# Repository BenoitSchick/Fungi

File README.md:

# Projet Fungi

The goal of this project is to measure the impedance of bags containing mycelium in order to observe how mycelium growth influences impedance. With this information, we aim to determine whether the mycelium is fully developed in the bags or if there are areas with little or no growth.

## Operation

The idea is to measure the impedance of the mycelium over several weeks to observe its evolution. Each measurement consists of a frequency sweep from 1 kHz to 100 kHz, taken every 5 minutes.  

The measurements from the Evaluation Board (EVAL-AD5940BIOZ) are retrieved via UART by a Raspberry Pi. The Raspberry Pi then synchronizes this data with Google Drive, making the measurements accessible from anywhere.

The measurement process is triggered by the Raspberry Pi. The reason for this is that up to four boards can be placed on the same bag, and the Raspberry Pi coordinates the measurements from each board to prevent interference.

## Material used
- Precision Impedance Analyzer - Agilent 4294A
- ECG Electrodes
- 4 x Bio-Electric Evaluation Board - EVAL-AD5940BIOZ
- Raspberry pi model 3B+

## Installation / Configuration
### Flashing the Evaluation Board

The first step is to install the Keil IDE to compile and program the Evaluation Board by following this setup guide: https://wiki.analog.com/resources/eval/user-guides/eval-ad5940/tools/keil_setup_guide  

The code used to program the evaluation board is located in the following folder: _Fungi/EVAL-AD590ELCZ_Pain/ad5940-examples-master/ad5940-examples-master/examples/AD5940_BIA_

This code is based on the official repository: https://github.com/analogdevicesinc/ad5940-examples  

With this code, the evaluation board performs a frequency sweep to measure impedance only when it receives a trigger signal on **pin GP4** from the Raspberry Pi.

### Raspberry Pi Configuration

The Raspberry Pi runs two Python scripts in the background, located in:  
_Fungi/EVAL-AD590ELCZ_Pain/python_Code_

- com_ports.py 
- Measurement_synchronization.py  

The first script retrieves data from each COM port to which the four AD5940 boards are connected. It stores the data in CSV files, one per COM port, in the folder: _Fungi/EVAL-AD590ELCZ_Pain/python_Code/Measurement_

The second script sends trigger pulses to the **GP4 pins** of the four evaluation boards to start measurements. It also coordinates measurements between the boards to avoid interference. Additionally, it synchronizes the data in the `Measurement` folder with a `measure_impedance` folder on Google Drive using `rclone`.

#### Python Installation

- Install Python 3 and pip:

```bash
sudo apt update && sudo apt upgrade -y
sudo apt install python3 python3-pip -y
```
- Create and activate a virtual environment:

```bash
python3 -m venv mon_env
source mon_env/bin/activate
```

- Install required libraries:
```bash
# Library for serial communication
pip install pyserial
# Library to control Raspberry Pi GPIO
pip install RPi.GPIO
```

#### Google Drive Remote Configuration
To synchronize the local `Measurement` folder with a remote folder on Google Drive, install and configure `rclone`:

```bash
# Install rclone
sudo apt install rclone
# Configure rclone
rclone config
```

#### Create Services to Run Python Scripts
The two python scripts (_com_ports.py_ and _Measurement_synchronization.py_) are run as background services on Linux. This ensures they start automatically when the Raspberry Pi powers on. The service files are located in: _/etc/systemd/system_

- *read_ports.service* : Runs _com_ports.py_

```bash
[Unit]
Description=Measurement System (Serial)
After=network.target

[Service]
ExecStart=/home/fr1boise/Documents/Fungi/EVAL-AD590ELCZ_Pain/python_Code/.venv/bin/python3 /home/fr1boise/Documents/Fungi/EVAL-AD590ELCZ_Pain/python_Code/com_ports.py
WorkingDirectory=/home/fr1boise/Documents/Fungi/EVAL-AD590ELCZ_Pain/python_Code
Restart=always
RestartSec=5
User=fr1boise

PrivilegesStartOnly=true

[Install]
WantedBy=multi-user.target
```
- *measure_syncro.service* : Runs _Measurement_synchronization.py_

```bash
[Unit]
Description=Measurement System (Synchronisation)
After=network.target

[Service]
ExecStart=/home/fr1boise/Documents/Fungi/EVAL-AD590ELCZ_Pain/python_Code/.venv/bin/python3 /home/fr1boise/Documents/Fungi/EVAL-AD590ELCZ_Pain/python_Code/Measurement_synchronization.py
WorkingDirectory=/home/fr1boise/Documents/Fungi/EVAL-AD590ELCZ_Pain/python_Code
Restart=always
RestartSec=5
User=fr1boise

PrivilegesStartOnly=true

[Install]
WantedBy=multi-user.target
```

- Commands to enable and start a service:

```bash
sudo systemctl enable name.service
sudo systemctl start name.service
```

# EVAL-AD777xFMCZ - Electrophysiological measurement
- *ad777.service* : Runs the ad777 executable

```bash
[Unit]
Description=Electrophysiological measurement (AD777)
After=network.target

[Service]
ExecStart=/home/fr1boise/Documents/Fungi/ADC/AD777_code/ad777
WorkingDirectory=/home/fr1boise/Documents/Fungi/ADC/AD777_code/
Restart=always
RestartSec=5
User=root

[Install]
WantedBy=multi-user.target
```

- *sync_ADC.sh* : Script to synchronize data on Google Drive
```bash
#!/bin/bash

mkdir -p /home/fr1boise/Documents/Fungi/adc_snapshot

rsync -a --delete --inplace \
/home/fr1boise/Documents/Fungi/ADC/AD777_code/Measurement_ADC/ \
/home/fr1boise/Documents/Fungi/adc_snapshot

rclone copy /home/fr1boise/Documents/Fungi/adc_snapshot gdrive:mesure_ADC \
  --transfers=4 \
  --fast-list \
  --drive-use-trash=false
```

# Tailscale
## Installation 

- Enable ssh server
```bash
sudo raspi-config
```

- Installation:
```bash
curl -fsSL https://tailscale.com/install.sh | sh
```
- start the Tailscale client
```bash
sudo tailscale up --ssh
```
if it don't work : 
```bash
sudo tailscale up --force-reauth
```

- connect to raspberry
```bash
ssh fr1boise@100.98.6.121
```

- Transfer file from Raspberry Pi to Laptop (Laptop and Raspberry must be added to tailscale)
```bash
scp /home/fr1boise/Documents/Fungi/adc_snapshot/channel0 beuns/@100.91.175.60:/home/beuns/Documents
```

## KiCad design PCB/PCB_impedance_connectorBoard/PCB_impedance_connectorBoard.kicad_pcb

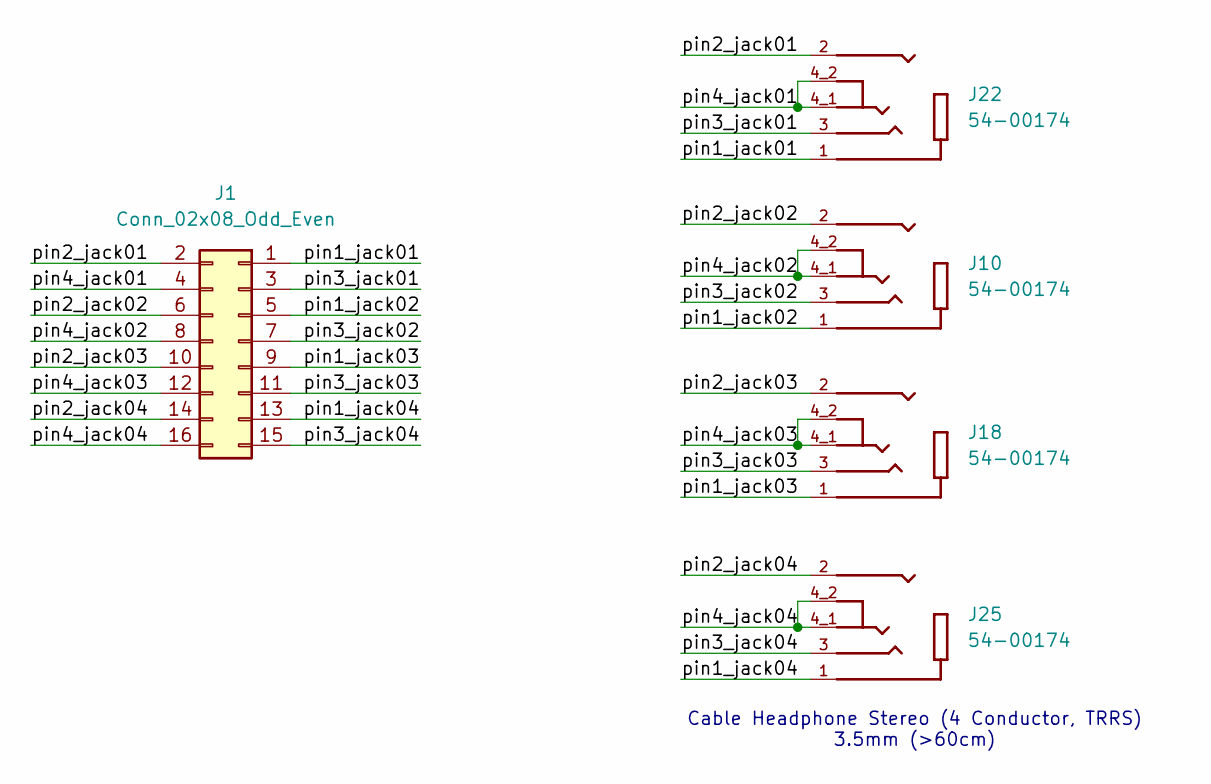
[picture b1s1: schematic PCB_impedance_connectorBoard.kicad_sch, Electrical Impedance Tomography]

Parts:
J1: Conn_02x08_Odd_Even; PinHeader_2x08_P2.54mm_Vertical; Manufacturer Part Number SSK03-MPH-254-B8; Digikey Pat Number 2223-SSK03-MPH-254-B8-ND
J10, J18, J22, J25: 54-00174; connJack_4cond_54-00174; Manufacturer Part Number 54-00174; Digikey Part Number 839-54-00174CT-ND

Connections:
/pin1_jack01: J1.1, J22.1
/pin1_jack02: J1.5, J10.1
/pin1_jack03: J1.9, J18.1
/pin1_jack04: J1.13, J25.1
/pin2_jack01: J1.2, J22.2
/pin2_jack02: J1.6, J10.2
/pin2_jack03: J1.10, J18.2
/pin2_jack04: J1.14, J25.2
/pin3_jack01: J1.3, J22.3
/pin3_jack02: J1.7, J10.3
/pin3_jack03: J1.11, J18.3
/pin3_jack04: J1.15, J25.3
/pin4_jack01: J1.4, J22.4_1, J22.4_2
/pin4_jack02: J1.8, J10.4_1, J10.4_2
/pin4_jack03: J1.12, J18.4_1, J18.4_2
/pin4_jack04: J1.16, J25.4_1, J25.4_2

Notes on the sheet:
Cable Headphone Stereo (4 Conductor, TRRS) 3.5mm (>60cm)

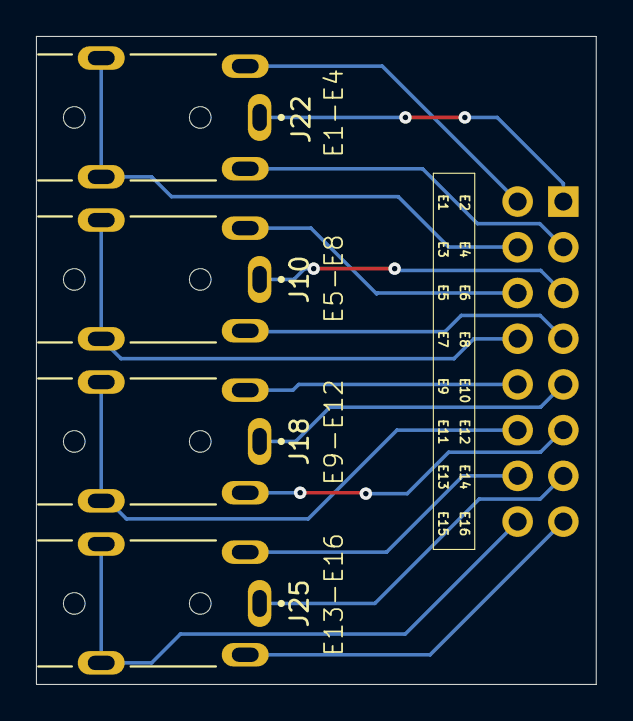
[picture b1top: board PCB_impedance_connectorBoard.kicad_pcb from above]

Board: 2 copper layers, 31.1 x 36.0 mm, 5 parts (1 on the bottom side), 16 nets.

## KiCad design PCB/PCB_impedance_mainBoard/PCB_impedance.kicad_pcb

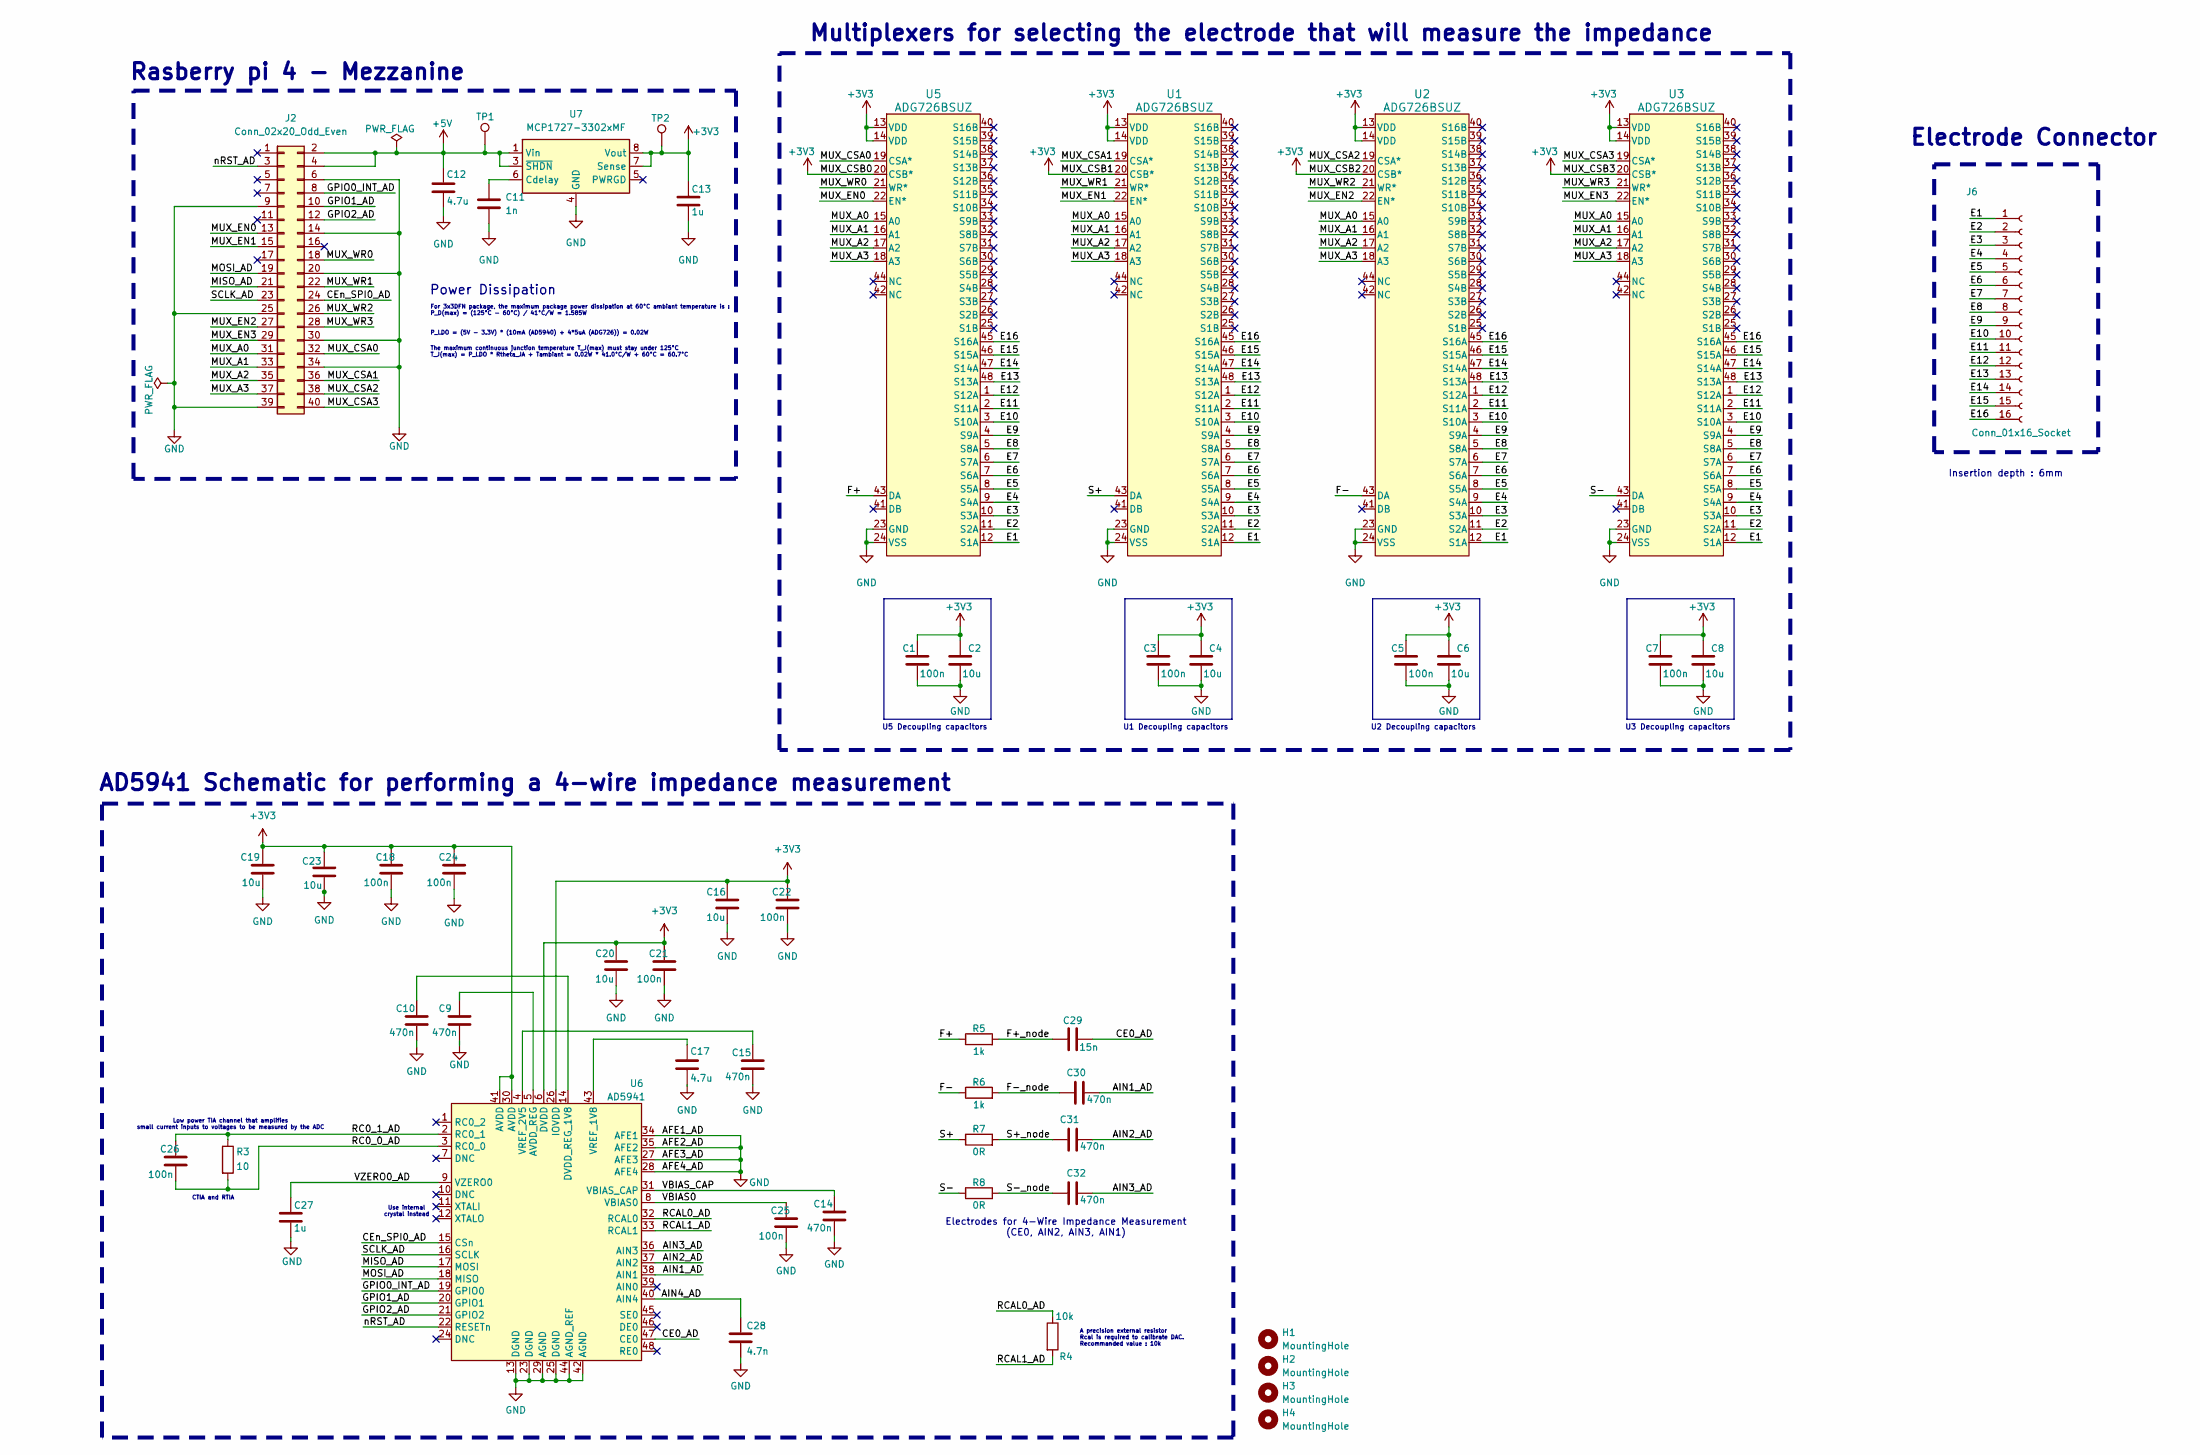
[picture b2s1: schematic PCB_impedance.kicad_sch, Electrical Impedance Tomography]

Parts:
C1, C3, C5, C7: 100n; C_0603_1608Metric; Manufacturer Part Number C0805F104K1RACAUTO; Digikey Part Number 399-C0805F104K1RACAUTODKR-ND
C2, C4, C6, C8: 10u; C_0603_1608Metric; Manufacturer Part Number GRM21BR71A106KA73K; Digikey Part Number 490-14381-6-ND
C9, C10, C14, C15, C30, C31, C32: 470n; C_0603_1608Metric; Manufacturer Part Number GCM188R71C474KA55D; Digikey Part Number 490-4775-6-ND
C11: 1n; C_0603_1608Metric; Manufacturer Part Number C0603C102K5RACTU; Digikey Part Number 399-C0603C102K5RACTUDKR-ND
C12, C17: 4.7u; C_0805_2012Metric; Manufacturer Part Number GRM21BR61H475KE51L; Digikey Part Number 490-10751-6-ND
C13, C27: 1u; C_0805_2012Metric; Manufacturer Part Number C0805C105K3RACTU; Digikey Part Number 399-C0805C105K3RACTUDKR-ND
C16, C19, C20, C23: 10u; C_0805_2012Metric; Manufacturer Part Number GRM21BR71A106KA73K; Digikey Part Number 490-14381-6-ND
C18, C21, C22, C24, C25, C26: 100n; C_0805_2012Metric; Manufacturer Part Number C0805F104K1RACAUTO; Digikey Part Number 399-C0805F104K1RACAUTODKR-ND
C28: 4.7n; C_0603_1608Metric; Manufacturer Part Number GRM1885C1H472JA01D; Digikey Part Number 490-9669-6-ND
C29: 15n; C_0603_1608Metric; Manufacturer Part Number C0603C153K5RACTU; Digikey Part Number 399-C0603C153K5RACTUDKR-ND
H1, H2, H3, H4: MountingHole; MountingHole_2.7mm_Pad
J2: Conn_02x20_Odd_Even; PinSocket_2x20_P2.54mm_Vertical
J6: Conn_01x16_Socket; conn_1x16_PPPC082LFBN-RC; Manufacturer Part Number PPPC082LFBN-RC; Digikey Part Number S7111-ND
R3: 10; R_0805_2012Metric; Manufacturer Part Number RT0805BRD0710RL; Digikey Part Number YAG4820DKR-ND
R4: 10k; R_0805_2012Metric; Manufacturer Part Number RT0805BRD0710KL; Digikey Part Number YAG1763DKR-ND
R5, R6: 1k; R_0805_2012Metric; Manufacturer Part Number RC0805FR-131KL; Digikey Part Number 13-RC0805FR-131KLDKR-ND
R7, R8: 0R; R_0805_2012Metric; Manufacturer Part Number RC0805JR-070RL; Digikey Part Number 311-0.0ARDKR-ND
TP1, TP2: TestPoint; TestPoint_Pad_D1.0mm
U1, U2, U3, U5: ADG726BSUZ; ADG726SBUZ; Manufacturer Part Number ADG726BSUZ; Digikey Part Number 505-ADG726BSUZ-ND
U6: AD5941; AD5941_footprint; Manufacturer Part Number AD5941BCPZ-RL7; Digikey Part Number 505-AD5941BCPZ-RL7DKR-ND
U7: MCP1727-3302xMF; DFN-8-1EP_3x3mm_P0.65mm_EP1.55x2.4mm; Manufacturer Part Number MCP1727T-3302E/MF; Digikey Part Number MCP1727T-3302E/MFDKR-ND

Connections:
+3V3: C1.1, C2.1, C3.1, C4.1, C5.1, C6.1, C7.1, C8.1, C13.1, C16.1, C18.1, C19.1, C20.1, C21.1, C22.1, C23.1, C24.1, TP2.1, U1.13 (VDD), U1.14 (VDD), U1.20 (CSB*), U2.13 (VDD), U2.14 (VDD), U2.20 (CSB*), U3.13 (VDD), U3.14 (VDD), U3.20 (CSB*), U5.13 (VDD), U5.14 (VDD), U5.20 (CSB*), U6.6 (DVDD), U6.26 (IOVDD), U6.30 (AVDD), U6.41 (AVDD), U7.7 (Sense), U7.8 (Vout)
+5V: C12.1, J2.2, J2.4, TP1.1, U7.1 (Vin), U7.2 (Vin), U7.3 (~SHDN)
/AIN1_AD: C30.1, U6.38 (AIN1)
/AIN2_AD: C31.1, U6.37 (AIN2)
/AIN3_AD: C32.1, U6.36 (AIN3)
/AIN4_AD: C28.1, U6.40 (AIN4)
/CE0_AD: C29.2, U6.47 (CE0)
/CEn_SPI0_AD: J2.24, U6.15 (CSn)
/E1: J6.1, U1.12 (S1A), U2.12 (S1A), U3.12 (S1A), U5.12 (S1A)
/E2: J6.2, U1.11 (S2A), U2.11 (S2A), U3.11 (S2A), U5.11 (S2A)
/E3: J6.3, U1.10 (S3A), U2.10 (S3A), U3.10 (S3A), U5.10 (S3A)
/E4: J6.4, U1.9 (S4A), U2.9 (S4A), U3.9 (S4A), U5.9 (S4A)
/E5: J6.5, U1.8 (S5A), U2.8 (S5A), U3.8 (S5A), U5.8 (S5A)
/E6: J6.6, U1.7 (S6A), U2.7 (S6A), U3.7 (S6A), U5.7 (S6A)
/E7: J6.7, U1.6 (S7A), U2.6 (S7A), U3.6 (S7A), U5.6 (S7A)
/E8: J6.8, U1.5 (S8A), U2.5 (S8A), U3.5 (S8A), U5.5 (S8A)
/E9: J6.9, U1.4 (S9A), U2.4 (S9A), U3.4 (S9A), U5.4 (S9A)
/E10: J6.10, U1.3 (S10A), U2.3 (S10A), U3.3 (S10A), U5.3 (S10A)
/E11: J6.11, U1.2 (S11A), U2.2 (S11A), U3.2 (S11A), U5.2 (S11A)
/E12: J6.12, U1.1 (S12A), U2.1 (S12A), U3.1 (S12A), U5.1 (S12A)
/E13: J6.13, U1.48 (S13A), U2.48 (S13A), U3.48 (S13A), U5.48 (S13A)
/E14: J6.14, U1.47 (S14A), U2.47 (S14A), U3.47 (S14A), U5.47 (S14A)
/E15: J6.15, U1.46 (S15A), U2.46 (S15A), U3.46 (S15A), U5.46 (S15A)
/E16: J6.16, U1.45 (S16A), U2.45 (S16A), U3.45 (S16A), U5.45 (S16A)
/F+: R5.1, U5.43 (DA)
/F+_node: C29.1, R5.2
/F-: R6.1, U2.43 (DA)
/F-_node: C30.2, R6.2
/GPIO0_INT_AD: J2.8, U6.19 (GPIO0)
/GPIO1_AD: J2.10, U6.20 (GPIO1)
/GPIO2_AD: J2.12, U6.21 (GPIO2)
/MISO_AD: J2.21, U6.17 (MOSI)
/MOSI_AD: J2.19, U6.18 (MISO)
/MUX_A0: J2.31, U1.15 (A0), U2.15 (A0), U3.15 (A0), U5.15 (A0)
/MUX_A1: J2.33, U1.16 (A1), U2.16 (A1), U3.16 (A1), U5.16 (A1)
/MUX_A2: J2.35, U1.17 (A2), U2.17 (A2), U3.17 (A2), U5.17 (A2)
/MUX_A3: J2.37, U1.18 (A3), U2.18 (A3), U3.18 (A3), U5.18 (A3)
/MUX_CSA0: J2.32, U5.19 (CSA*)
/MUX_CSA1: J2.36, U1.19 (CSA*)
/MUX_CSA2: J2.38, U2.19 (CSA*)
/MUX_CSA3: J2.40, U3.19 (CSA*)
/MUX_EN0: J2.13, U5.22 (EN*)
/MUX_EN1: J2.15, U1.22 (EN*)
/MUX_EN2: J2.27, U2.22 (EN*)
/MUX_EN3: J2.29, U3.22 (EN*)
/MUX_WR0: J2.18, U5.21 (WR*)
/MUX_WR1: J2.22, U1.21 (WR*)
/MUX_WR2: J2.26, U2.21 (WR*)
/MUX_WR3: J2.28, U3.21 (WR*)
/RC0_0_AD: C26.2, R3.2, U6.3 (RC0_0)
/RC0_1_AD: C26.1, R3.1, U6.2 (RC0_1)
/RCAL0_AD: R4.1, U6.32 (RCAL0)
/RCAL1_AD: R4.2, U6.33 (RCAL1)
/S+: R7.1, U1.43 (DA)
/S+_node: C31.2, R7.2
/S-: R8.1, U3.43 (DA)
/S-_node: C32.2, R8.2
/SCLK_AD: J2.23, U6.16 (SCLK)
/VBIAS0: C25.1, U6.8 (VBIAS0)
/VBIAS_CAP: C14.1, U6.31 (VBIAS_CAP)
/VZERO0_AD: C27.1, U6.9 (VZERO0)
/nRST_AD: J2.3, U6.22 (RESETn)
GND: C1.2, C2.2, C3.2, C4.2, C5.2, C6.2, C7.2, C8.2, C9.2, C10.2, C11.2, C12.2, C13.2, C14.2, C15.2, C16.2, C17.2, C18.2, C19.2, C20.2, C21.2, C22.2, C23.2, C24.2, C25.2, C27.2, C28.2, J2.6, J2.9, J2.14, J2.20, J2.25, J2.30, J2.34, J2.39, U1.23 (GND), U1.24 (VSS), U2.23 (GND), U2.24 (VSS), U3.23 (GND), U3.24 (VSS), U5.23 (GND), U5.24 (VSS), U6.13 (DGND), U6.23 (DGND), U6.25 (DGND), U6.27 (AFE3), U6.28 (AFE4), U6.29 (AGND), U6.34 (AFE1), U6.35 (AFE2), U6.42 (AGND), U6.44 (AGND_REF), U7.4 (GND), U7.9 (GND)
unnamed: C9.1, U6.5 (AVDD_REG)
unnamed: C10.1, U6.14 (DVDD_REG_1V8)
unnamed: C17.1, U6.43 (VREF_1V8)
unnamed: C15.1, U6.4 (VREF_2V5)
unnamed: C11.1, U7.6 (Cdelay)

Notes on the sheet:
Use internal crystal instead
Low power TIA channel that amplifies small current inputs to voltages to be measured by the ADC
A precision external resistor Rcal is required to calibrate DAC. Recommanded value : 10k
For 3x3DFN package, the maximum package power dissipation at 60°C ambiant temperature is : P_D(max) = (125°C - 60°C) / 41°C/W = 1.585W
Electrodes for 4-Wire Impedance Measurement (CE0, AIN2, AIN3, AIN1)
Rasberry pi 4 - Mezzanine
Electrode Connector
U2 Decoupling capacitors
P_LDO = (5V - 3.3V) * (10mA (AD5940) + 4*5uA (ADG726)) = 0.02W
The maximum continuous junction temperature T_J(max) must stay under 125°C T_J(max) = P_LDO * Rtheta_JA + Tambiant = 0.02W * 41.0°C/W + 60°C = 60.7°C
CTIA and RTIA
Power Dissipation
U5 Decoupling capacitors
U3 Decoupling capacitors
U1 Decoupling capacitors
Multiplexers for selecting the electrode that will measure the impedance
Insertion depth : 6mm
AD5941 Schematic for performing a 4-wire impedance measurement

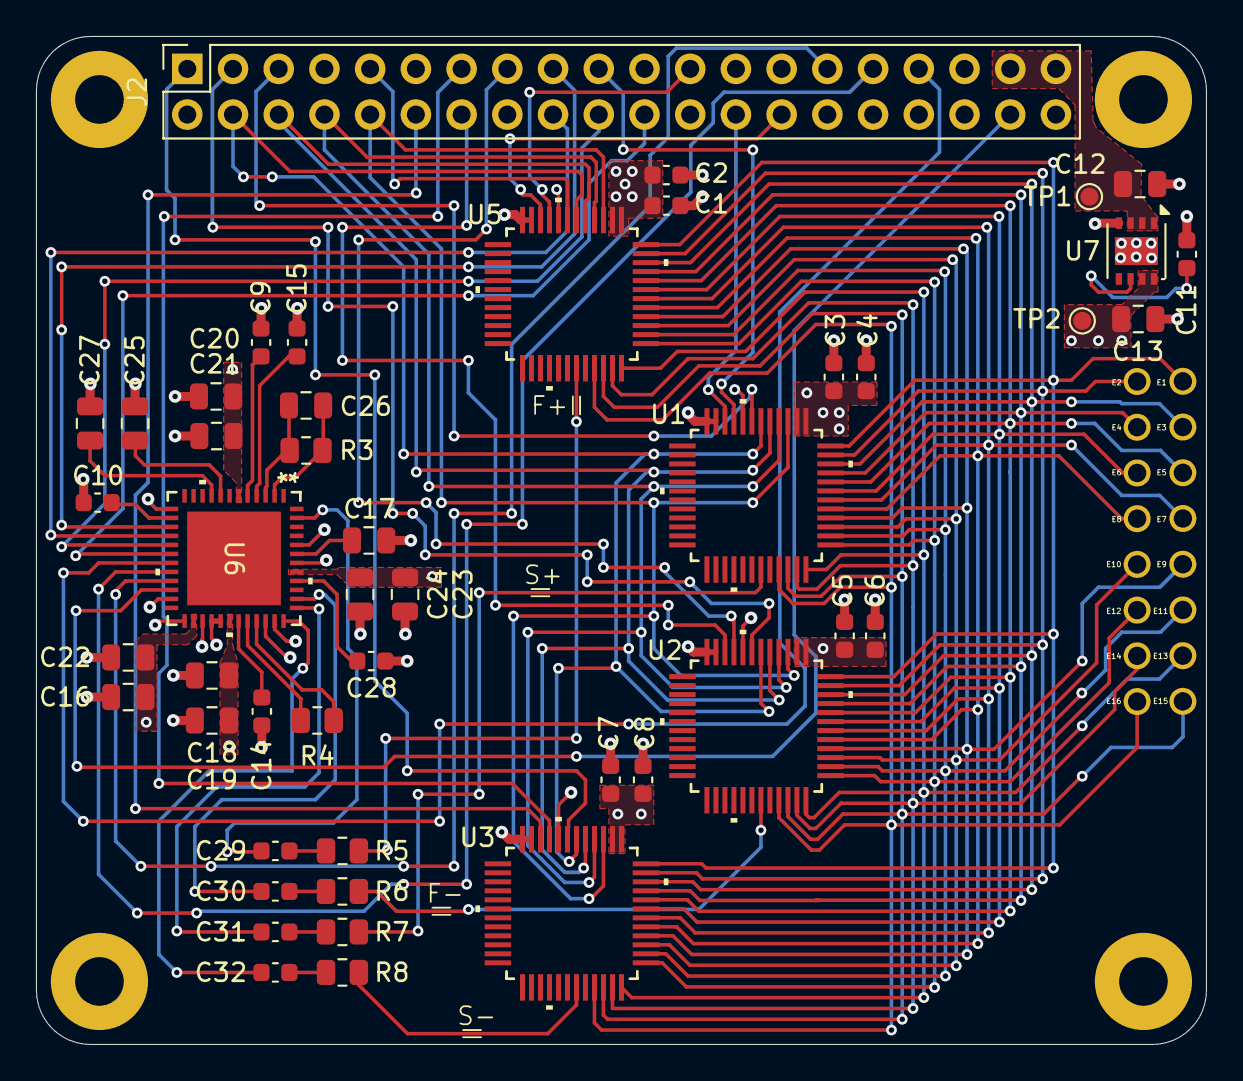
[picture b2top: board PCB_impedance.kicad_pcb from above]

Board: 4 copper layers, 65.0 x 56.0 mm, 52 parts (1 on the bottom side), 68 nets.

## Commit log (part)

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2026-03-04 update conclusion
2026-03-11 add python script for com port reading
2026-03-16 fix: correction to identify the port
2026-03-16 configure remote google drive folder
2026-03-16 remove Allcom csv file
2026-03-23 clean project
2026-03-25 trigger sweep measurement with GPIO4
2026-03-25 update crontab
2026-03-25 remove waiting when reading com port
2026-03-27 Add files via upload
    Calcule de la taille minimale de la dropbox pour 2 semaines de mesures avec 4 cartes AD5940
2026-03-27 add cmd for wifi
2026-03-27 add wifi cmd to python script used for synchronization
2026-03-27 add thread for control GPIO
2026-03-27 limit OSR to 5
2026-03-29 add time before scanning com port
2026-03-29 add more time
2026-03-29 rename file
2026-03-30 remove the possibilty of desactivate wifi before taking measurement
2026-04-01 add 30min crontab
2026-04-01 add service for execute measure_synchronisation.py
2026-04-01 add wifi
2026-04-06 Add sync_rclone to Measurement_synchronisation.py
2026-04-13 Add logging + restarts the service if a thread crashes (com_port.py)
2026-04-13 Update queue size log (com_port.py)
2026-04-13 Restart service if USB port added/removed (com_ports.py)
2026-04-15 clean
2026-04-15 README : install toolchain - raspberry pi pico
2026-04-15 update gitignore
2026-04-17 WIP : driver AD777 for PICO
2026-04-20 feat: add AD777x driver skeleton for Raspberry Pi Pico
2026-04-27 Add ADC code
2026-04-27 adc777 code for raspberry pi
2026-04-27 clean files
2026-04-29 clean files + makefile for AD777 source code
2026-04-29 add debug message
2026-04-29 fix: brace missing
2026-04-29 add folder for ADC measurement
2026-05-01 change save directory
2026-05-04 Add timestamp file
2026-05-04 add folder Measurement_ADC
2026-05-04 python script to read binary data
2026-05-04 mesure channel 0
2026-05-04 4 channels active on progress
2026-05-04 4 channels active on progress 01
2026-05-04 dimensionnement kSPS
2026-05-04 Reduce 8 channels ADC to 4 channels ADC
2026-05-04 mesure 4 channels
2026-05-11 configure ADC - 8 channels at 1kSPS
2026-05-11 configure storage frequency at 125 samples/s
2026-05-13 first measure
2026-05-13 update script read_binaryData
2026-05-20 add files
2026-05-20 test Raspberry pi SPI
2026-05-22 debug SPI - WIP
2026-05-27 rclone for ADC
2026-05-27 bug rclone
2026-05-27 script for sync file with google drive
2026-05-27 update script for sync ADC data with google drive
2026-05-27 remove error file
2026-05-27 bug fixed for synchronize data in google drive
2026-05-27 script for plotting ADC data
2026-05-27 fix: google drive doesnt put file in trash can anymore
2026-06-01 Replace "wb" by "ab" when opening file (otherwise it overwrites the data)
2026-06-03 error: rclone can't transfer file to google drive
2026-06-10 tailscale installation
2026-06-10 update README - ssh access via tailscale
2026-06-11 Update README : connect to raspberry pi via tailscale
2026-06-19 Schematic (PCB) for impedance measurement - Need a review
2026-06-19 Results of the two measurements taken (April 24 to May 18 – June 3 to June 18)
2026-06-19 add footprint
2026-06-24 Graphs from the second set of measurements (June 3 to June 24)
2026-06-26 Presentation finalized for fungi meeting
2026-06-26 Correction to the PCB schematic for measuring impedance (replacement of the multiplexer and add new connector for electrodes)
2026-06-29 Multiplexer routing complete
